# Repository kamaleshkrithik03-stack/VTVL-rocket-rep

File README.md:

# My VTVL electric rocket!
This project has been  a lifelong dream of mine to be honest. Ive been trying for a lot of time now but I coudnt make tangible progress due to financial issues. Now thanks to fabriccate and hack club i got a chance i dont want to waste. My inspiration was from BPS space and i truly love that youtube cahnnel

## Build details
I initially planned on using a actual f class engine but due to legal issues and tight budget(for me) i eventually got an idea of using a dual bldc anti coaxial(thats the word i beleieve ) setup to avoid roll issues(connservation of angular momentum). For now this is liminted to my tvc model and flight controller with electronics.
##A pic of my PCB

## The TVC design
### REVIEWERS PLEASE NOTE THAT THE MOTOR SEEN IN THIS IMAGE WILL BE USED IN ANOTHER PROJECT AND I CAN USE THE PROPELLORS FOR THIS PROJECT WHICH IS ALSO STILL NOT COMPLETELY NECCESSARY

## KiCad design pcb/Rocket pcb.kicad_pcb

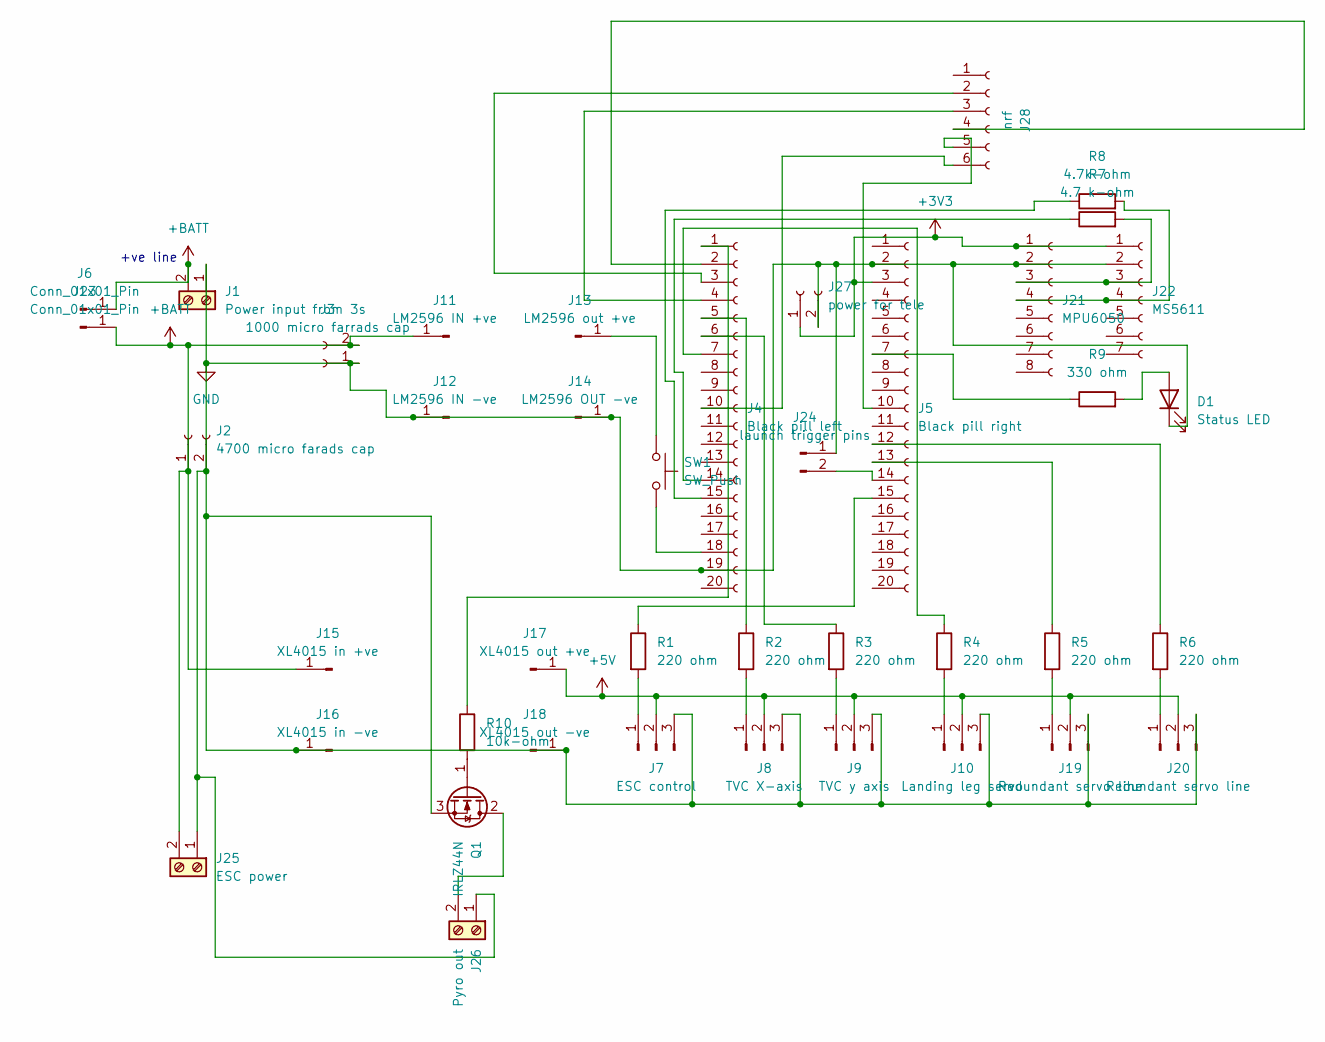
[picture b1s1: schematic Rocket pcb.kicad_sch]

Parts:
D1: Status LED; LED_1206_3216Metric
J1: Power input from 3s; TerminalBlock_Phoenix_MKDS-1,5-2-5.08_1x02_P5.08mm_Horizont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
J2: 4700 micro farads cap; PinSocket_1x02_P2.54mm_Vertical
J3: 1000 micro farrads cap; PinSocket_1x02_P2.54mm_Vertical
J4: Black pill left; PinSocket_1x20_P2.54mm_Vertical
J5: Black pill right; PinSocket_1x20_P2.54mm_Vertical
J6, J23: Conn_01x01_Pin; PinHeader_1x01_P2.54mm_Vertical
J7: ESC control; PinHeader_1x03_P2.54mm_Vertical
J8: TVC X-axis; PinHeader_1x03_P2.54mm_Vertical
J9: TVC y axis; PinHeader_1x03_P2.54mm_Vertical
J10: Landing leg servo; PinHeader_1x03_P2.54mm_Vertical
J11: LM2596 IN +ve; PinHeader_1x01_P2.54mm_Vertical
J12: LM2596 IN -ve; PinHeader_1x01_P2.54mm_Vertical
J13: LM2596 out +ve; PinHeader_1x01_P2.54mm_Vertical
J14: LM2596 OUT -ve; PinHeader_1x01_P2.54mm_Vertical
J15: XL4015 in +ve; PinHeader_1x01_P2.54mm_Vertical
J16: XL4015 in -ve; PinHeader_1x01_P2.54mm_Vertical
J17: XL4015 out +ve; PinHeader_1x01_P2.54mm_Vertical
J18: XL4015 out -ve; PinHeader_1x01_P2.54mm_Vertical
J19, J20: Redundant servo line; PinHeader_1x03_P2.54mm_Vertical
J21: MPU6050; PinSocket_1x08_P2.54mm_Vertical
J22: MS5611; PinSocket_1x07_P2.54mm_Vertical
J24: launch trigger pins; PinHeader_1x02_P2.54mm_Vertical
J25: ESC power; TerminalBlock_Phoenix_MKDS-1,5-2-5.08_1x02_P5.08mm_Horizont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
J26: Pyro out; TerminalBlock_Phoenix_MKDS-1,5-2-5.08_1x02_P5.08mm_Horizont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
J27: power for tele; PinSocket_1x02_P2.54mm_Vertical
J28: nrf; PinSocket_1x06_P2.54mm_Vertical
Q1: IRLZ44N; TO-220-3_Vertical
R1, R2, R3, R4, R5, R6: 220 ohm; R_0805_2012Metric_Pad1.20x1.40mm_HandSolder
R7: 4.7 k-ohm; R_0805_2012Metric_Pad1.20x1.40mm_HandSolder
R8: 4.7k-ohm; R_0805_2012Metric_Pad1.20x1.40mm_HandSolder
R9: 330 ohm; R_0805_2012Metric_Pad1.20x1.40mm_HandSolder
R10: 10k-ohm; R_0805_2012Metric_Pad1.20x1.40mm_HandSolder
SW1: SW_Push; SW_PUSH_6mm

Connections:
+3V3: J5.3, J21.1, J22.1, J27.1
+5V: J7.2, J8.2, J9.2, J10.2, J17.1 (Pin_1_1), J19.2, J20.2
+BATT: J1.2, J2.1, J3.2, J6.1 (Pin_1_1), J11.1 (Pin_1_1), J15.1 (Pin_1_1), J23.1 (Pin_1_1), J25.2
GND: D1.1 (K), J1.1, J2.2, J3.1, J4.19, J5.2, J7.3, J8.3, J9.3, J10.3, J12.1 (Pin_1_1), J14.1 (Pin_1_1), J16.1 (Pin_1_1), J18.1 (Pin_1_1), J19.3, J20.3, J21.2, J22.2, J24.1, J25.1, J26.1, J27.2, Q1.3 (S)
unnamed: D1.2 (A), R9.2
unnamed: J4.1, R10.1
unnamed: J4.5, R2.1
unnamed: J4.6, R3.1
unnamed: J4.7, R4.1
unnamed: J4.14, R7.1
unnamed: J4.15, R8.1
unnamed: J4.18, SW1.2
unnamed: J5.7, R9.1
unnamed: J5.12, R6.1
unnamed: J5.13, R5.1
unnamed: J5.15, R1.1
unnamed: J7.1, R1.2
unnamed: J8.1, R2.2
unnamed: J9.1, R3.2
unnamed: J10.1, R4.2
unnamed: J13.1 (Pin_1_1), SW1.1
unnamed: J19.1, R5.2
unnamed: J20.1, R6.2
unnamed: J21.3, J22.3, R7.2
unnamed: J21.4, J22.4, R8.2
unnamed: J5.14, J24.2
unnamed: J26.2, Q1.2 (D)
unnamed: J4.3, J28.2
unnamed: J4.4, J28.3
unnamed: J4.2, J28.4
unnamed: J5.10, J28.5
unnamed: J4.10, J28.6
unnamed: Q1.1 (G), R10.2

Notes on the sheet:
+ve line

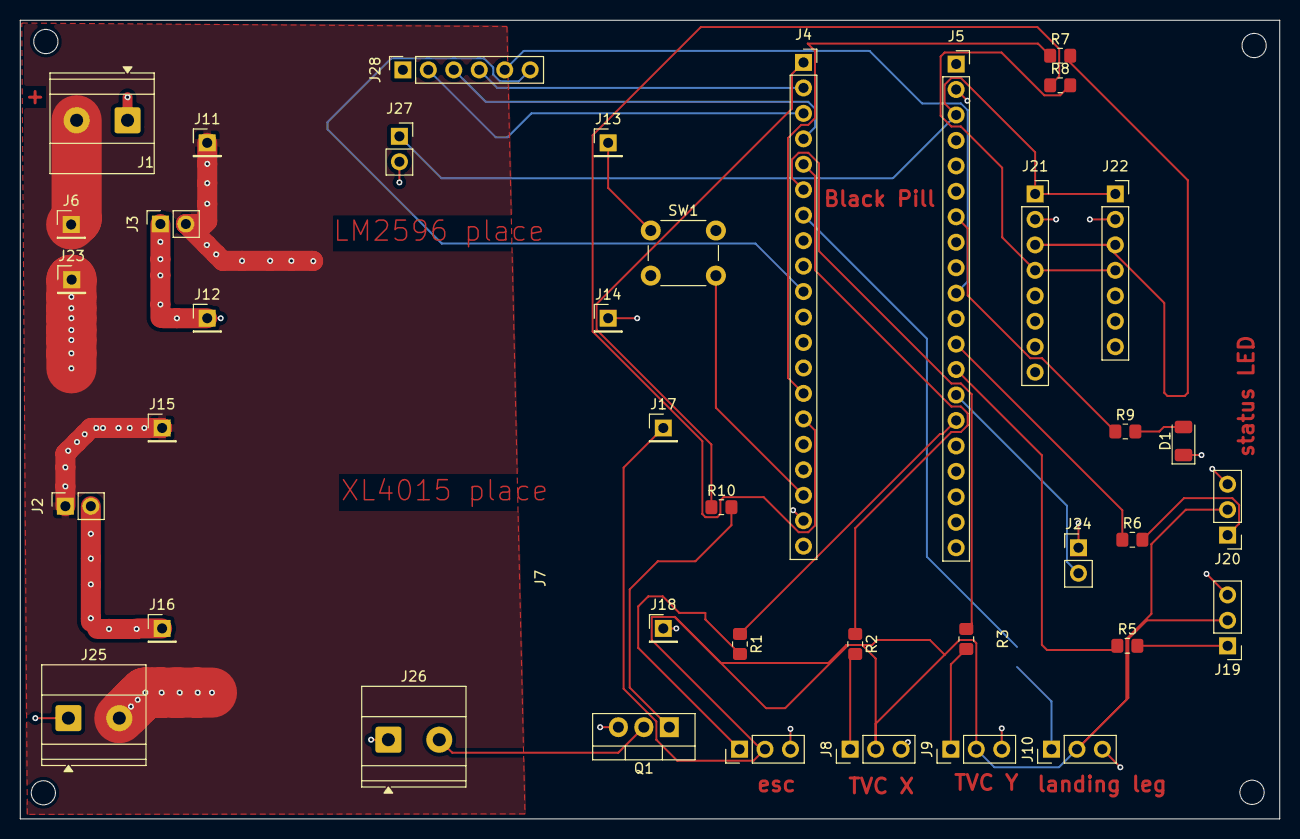
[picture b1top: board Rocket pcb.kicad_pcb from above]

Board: 4 copper layers, 125.7 x 79.7 mm, 41 parts (1 on the bottom side), 33 nets.
